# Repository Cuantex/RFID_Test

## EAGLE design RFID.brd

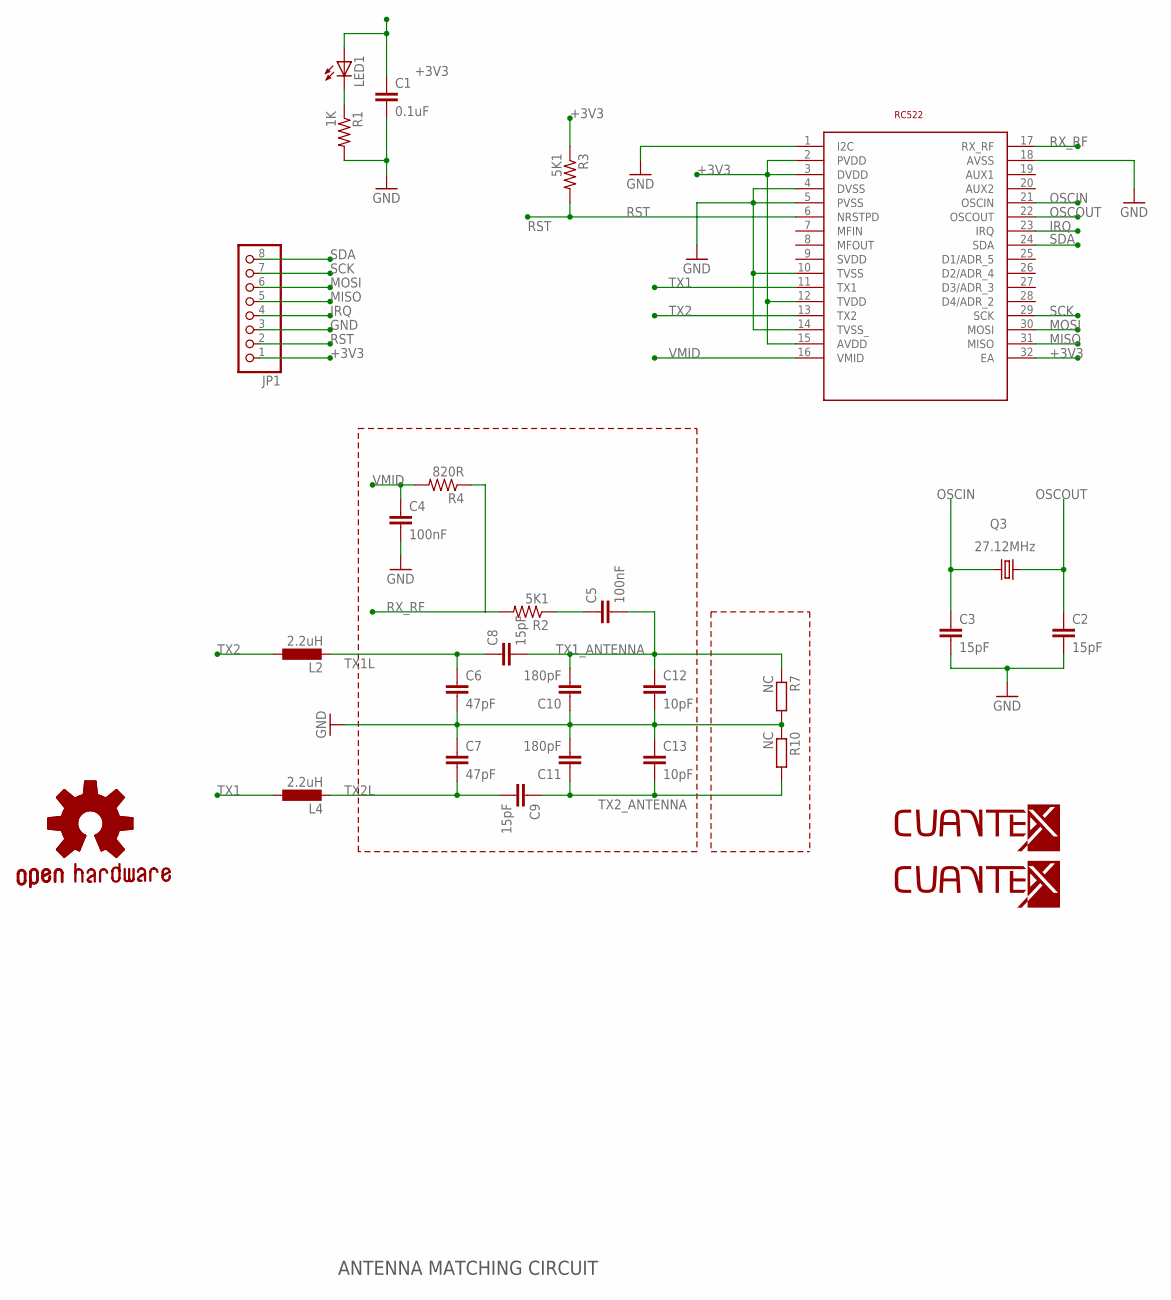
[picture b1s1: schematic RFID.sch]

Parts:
C1: 0.1uF; C0603K
C2, C3, C8, C9: 15pF; C0603K
C4, C5: 100nF; C0603K
C6, C7: 47pF; C0603K
C10, C11: 180pF; C0603K
C12, C13: 10pF; C0603K
GOLD_ORB_SM1: OSHWLOGO_GOLD_ORB_SM; OSHW2
JP1: PINHD-1X8; 1X08
L2, L4: 2.2uH; L2012C
LED1: LED_E; LED_1206
Q3: 27.12MHz; HC49UP
R1: 1K; R0603
R2, R3: 5K1; R0603
R4: 820R; R0603
R7, R10: NC; R0201
U1: RC522; HVQFN32
U$1: LOGO-BOT-50MM; B-50
U$2: LOGO-TOP-20MM; C-0

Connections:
+3V3: C1.1, JP1.1, LED1.A, R3.1, U1.2 (PVDD), U1.3 (DVDD), U1.12 (TVDD), U1.15 (AVDD), U1.32 (EA)
GND: C1.2, C2.2, C3.2, C4.2, C6.2, C7.1, C10.1, C11.2, C12.2, C13.1, JP1.3, R1.2, R7.2, R10.1, U1.1 (I2C), U1.4 (DVSS), U1.5 (PVSS), U1.10 (TVSS), U1.14 (TVSS_), U1.18 (AVSS)
IRQ: JP1.4, U1.23 (IRQ)
MISO: JP1.5, U1.31 (MISO)
MOSI: JP1.6, U1.30 (MOSI)
unnamed: LED1.C, R1.1
unnamed: C5.1, R2.1
OSCIN: C3.1, Q3.2, U1.21 (OSCIN)
OSCOUT: C2.1, Q3.1, U1.22 (OSCOUT)
RST: JP1.2, R3.2, U1.6 (NRSTPD)
RX_RF: R2.2, R4.1, U1.17 (RX_RF)
SCK: JP1.7, U1.29 (SCK)
SDA: JP1.8, U1.24 (SDA)
TX1: L4.1, U1.11 (TX1)
TX1L: C6.1, C8.1, L2.2
TX1_ANTENNA: C5.2, C8.2, C10.2, C12.1, R7.1
TX2: L2.1, U1.13 (TX2)
TX2L: C7.2, C9.2, L4.2
TX2_ANTENNA: C9.1, C11.1, C13.2, R10.2
VMID: C4.1, R4.2, U1.16 (VMID)

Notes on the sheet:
ANTENNA MATCHING CIRCUIT

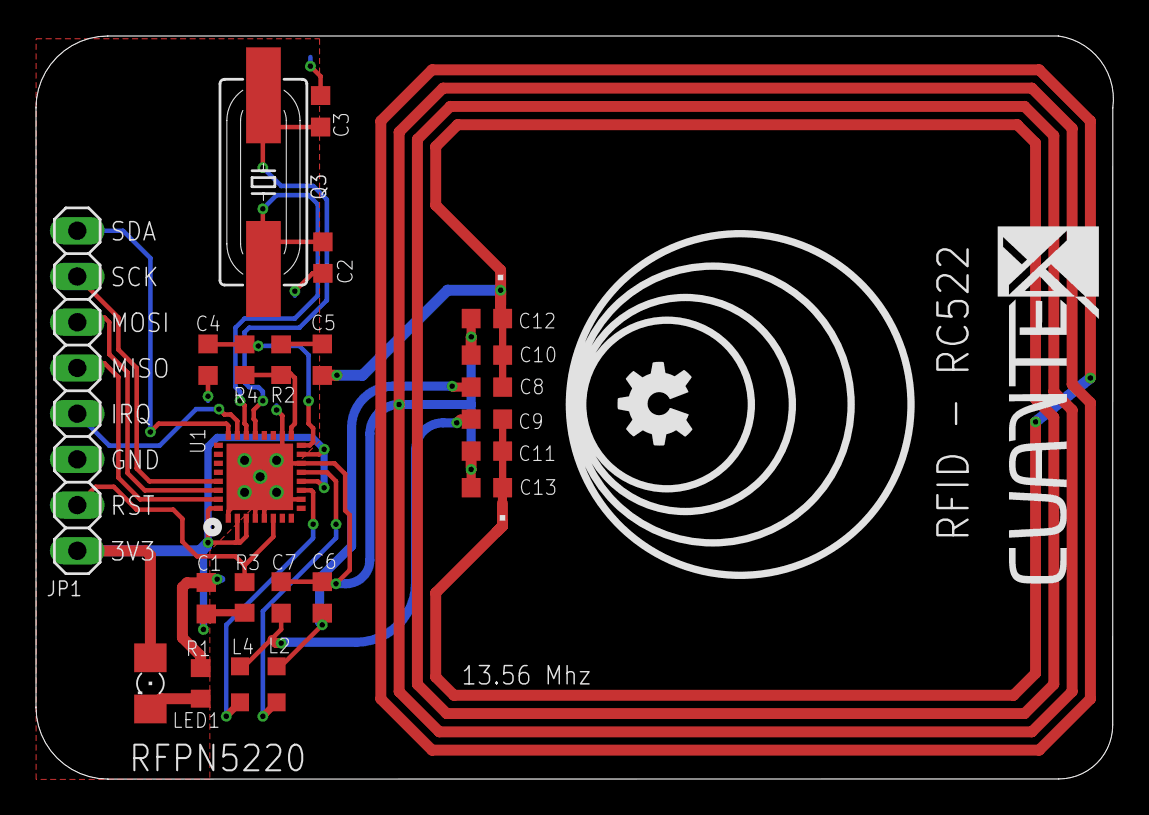
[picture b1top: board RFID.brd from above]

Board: 2 copper layers, 59.9 x 41.3 mm, 28 parts (0 on the bottom side), 20 nets.

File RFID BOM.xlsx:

Qty | Value | Device | Package | Parts | Description
1 |  | LED_E | LED_1206 | LED1 | LED
1 |  | PINHD-1X8 | 1X08 | JP1 | PIN HEADER
1 | 0.1uF | C-EUC0603K | C0603K | C1 | CAPACITOR, European symbol
2 | 100nF | C-EUC0603K | C0603K | C4, C5 | CAPACITOR, European symbol
2 | 10pF | C-EUC0603K | C0603K | C12, C13 | CAPACITOR, European symbol
4 | 15pF | C-EUC0603K | C0603K | C2, C3, C8, C9 | CAPACITOR, European symbol
2 | 180pF | C-EUC0603K | C0603K | C10, C11 | CAPACITOR, European symbol
1 | 1K | R-US_R0603 | R0603 | R1 | RESISTOR, American symbol
2 | 2.2uH | L-EUL2012C | L2012C | L2, L4 | INDUCTOR, European symbol
1 | 27.12MHz | CRYSTALHC49UP | HC49UP | Q3 | CRYSTAL
2 | 47pF | C-EUC0603K | C0603K | C6, C7 | CAPACITOR, European symbol
2 | 5K1 | R-US_R0603 | R0603 | R2, R3 | RESISTOR, American symbol
1 | 820R | R-US_R0603 | R0603 | R4 | RESISTOR, American symbol
2 | NC | R-EU_R0201 | R0201 | R7, R10 | RESISTOR, European symbol
1 | RC522 | RC522 | HVQFN32 | U1

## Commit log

2016-02-12 Archivos en Git2
